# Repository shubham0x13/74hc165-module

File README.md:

# 74HC165 Daisy-Chainable Shift Register Module - Rev 2.0

A simple, compact,  daisy-chainable breakout module based on the **74HC165 8-bit parallel-in/serial-out shift register**. It allows you to add digital inputs to any microcontroller in multiples of 8, using only 3 GPIO pins plus power and ground.

> [!NOTE]
> **Revision History:** Rev 2.0 is the first published release. The unpublished Rev 1.0 had a mirrored input header—while it worked standalone, daisy-chaining with a standard straight-through JST cable would short `VCC` to `GND`. Both headers now share the exact same pin order for safe, plug-and-play chaining. Rev 2.0 also changes the `DIN` termination from a pull-down to a pull-up to align with the default unpressed state of the input pins.

<!-- markdownlint-disable MD033 -->
<div align="center">
  
  &emsp;&emsp;&emsp;&emsp;&emsp;
  
</div>
<!-- markdownlint-enable MD033 -->

## Features & Specs

* **Inputs:** 8 digital inputs via two 5-pin JST-XH headers (4 inputs + shared GND per header).
* **Daisy-Chain:** Connect modules in series to expand inputs in multiples of 8, sharing the same `CLK`, `LOAD`, `VCC`, and `GND` lines.
* **Passives:** Onboard 10 kΩ pull-ups on all inputs, a 100 kΩ pull-up on `DIN` (to ensure that if the MCU reads more bits than are physically connected, the floating/ghost values default to 1, matching the unpressed state of the buttons), and a 100 nF decoupling capacitor.
* **Power:** 2.0V – 6.0V. **Use a VCC compatible with your microcontroller's logic levels** (e.g., 3.3 V for RP2040/ESP32, 5 V for standard Arduino).
* **Dimensions:** 35 × 35 mm (Four M3 mounting holes at 27 × 27 mm).
* **Compatibility:** Standard 74HC165 logic — compatible with DIY firmware such as **FreeJoy** and standard shift-register libraries for **Arduino** (`shiftIn`), **CircuitPython** (`adafruit_74hc165`), and other platforms.

## Pinout

### Chaining Headers (J1 & J2)

Both 5-pin headers share the same pin layout:

1. **VCC:** Power (Match your MCU logic level)
2. **LOAD:** Parallel Load / Latch
3. **CLK:** Clock
4. **DATA:** Serial Data (`DIN` on J1, `DOUT` on J2)
5. **GND:** Ground

**Wiring Guide:**

* **Single Module:** Connect **J2** to your microcontroller. Leave **J1** empty.
* **Daisy-Chaining:** Connect MCU ➔ **J2** (Module 1). Plug Module 1's **J1** ➔ **J2** (Module 2). Repeat for additional modules.

### Button Headers (J3 & J4)

* **D0–D7:** Digital inputs for your buttons/switches.
* **GND:** Shared ground pins.

> [!NOTE]
> Inputs have hardware pull-ups (active-low). Wire your switches directly between `Dx` and `GND`. The MCU will read `1` (HIGH) when open, and `0` (LOW) when pressed.

## Manufacturing & Downloads

<!-- markdownlint-disable MD033 -->
<p align="center">
  
  &emsp;&emsp;
  
</p>
<!-- markdownlint-enable MD033 -->

Ready-to-order fabrication files are available in the [Releases](https://github.com/shubham0x13/74hc165-module/releases) tab. Each release includes:

* **Gerber `.zip` files** (Single board & 4-board panel)
* **Assembly BOMs** (Interactive HTML BOM for easy hand-soldering, plus standard CSV)
* **Schematic PDF** & **STEP 3D Model**

> [!IMPORTANT]
> The 4-board panel (75 × 91 mm) is generated via KiKit and outputs V-score/cut lines on the `User.Comments` layer by default. When ordering the panel, ensure this layer is included in your Gerbers and explicitly request **V-scoring** in your order notes.

## Build Automation

To easily regenerate artifacts after modifying the PCB, a [justfile](justfile) is provided. It uses the KiCad CLI, KiKit, and InteractiveHtmlBom to generate the panel layout, Gerbers, STEP model, BOMs, schematic PDF, and 3D renders.

**Requirements:**

* [KiCad 10.0+](https://www.kicad.org/) (`kicad-cli` must be available in `PATH`)
* [just](https://just.systems/) command runner
* Python 3.10+ (Linux/macOS; Windows uses KiCad's bundled Python)
* [KiKit](https://github.com/yaqwsx/KiKit) (v1.8.1+)
* [InteractiveHtmlBom](https://github.com/openscopeproject/InteractiveHtmlBom) (v2.12.0+)
* **Windows:** Git for Windows (must be in your system PATH to provide `sh.exe` for commands like `rm` and `mkdir`).

**Usage:**

The build system is self-documenting. Run `just` from the repository root to see a list of all available commands and what they do.

```bash
# See all available build commands
just
```

## License

This project is open-source hardware licensed under the **CERN-OHL-S v2**. See [LICENSE](LICENSE) for details.

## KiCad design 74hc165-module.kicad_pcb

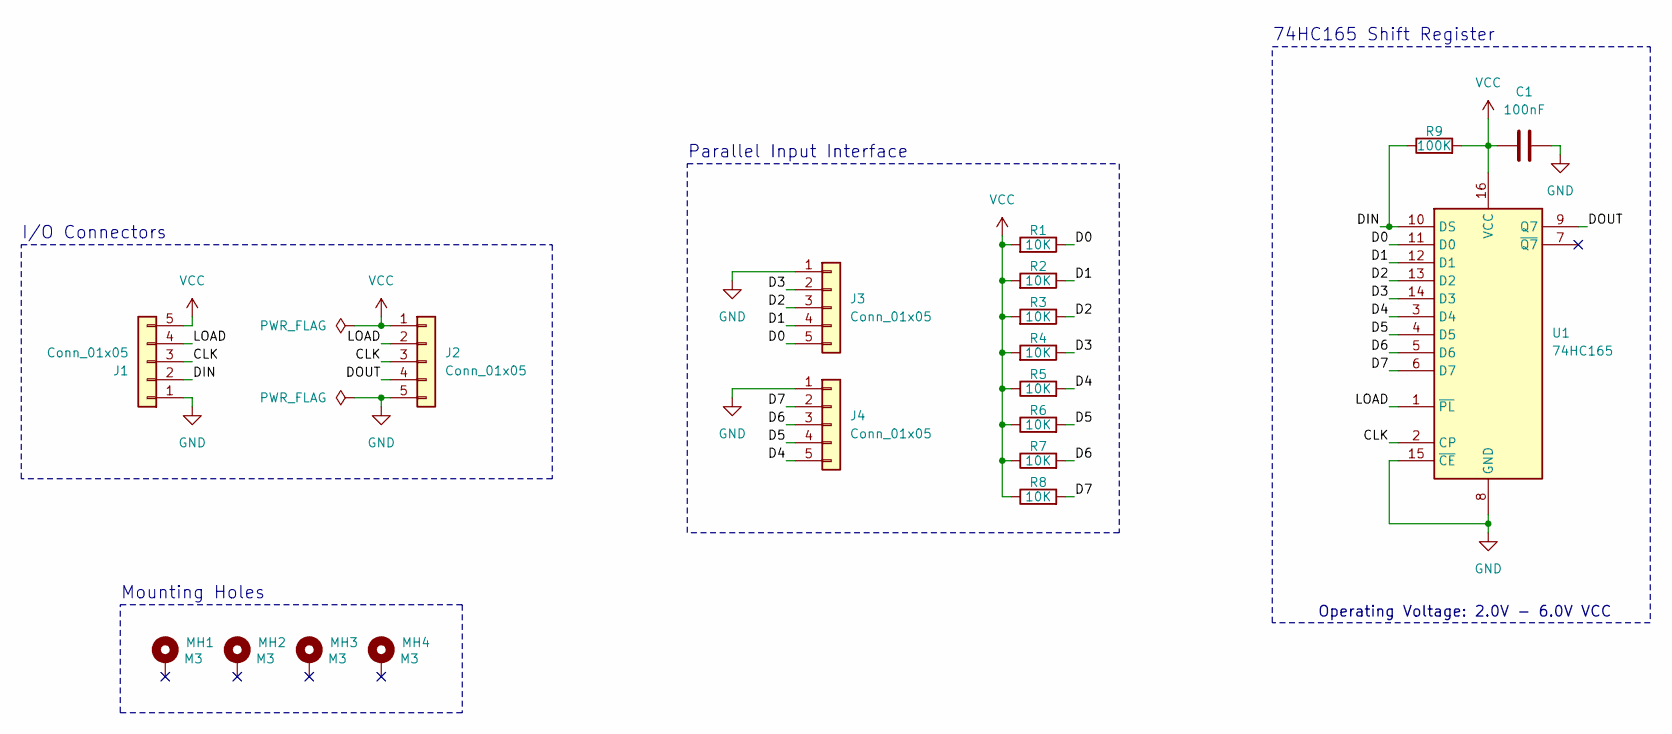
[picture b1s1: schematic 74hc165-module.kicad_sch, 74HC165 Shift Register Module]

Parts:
C1: 100nF; C_0603_1608Metric_Pad1.08x0.95mm_HandSolder
J1, J2, J3, J4: Conn_01x05; JST_XH_B5B-XH-A_1x05_P2.50mm_Vertical
MH1, MH2, MH3, MH4: M3; MountingHole_3.2mm_M3_Pad
R1, R2, R3, R4, R5, R6, R7, R8: 10K; R_0603_1608Metric_Pad0.98x0.95mm_HandSolder
R9: 100K; R_0603_1608Metric_Pad0.98x0.95mm_HandSolder
U1: 74HC165; SOIC-16_3.9x9.9mm_P1.27mm

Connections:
/CLK: J1.3, J2.3, U1.2 (CP)
/D0: J3.5, R1.1, U1.11 (D0)
/D1: J3.4, R2.1, U1.12 (D1)
/D2: J3.3, R3.1, U1.13 (D2)
/D3: J3.2, R4.1, U1.14 (D3)
/D4: J4.5, R5.2, U1.3 (D4)
/D5: J4.4, R6.2, U1.4 (D5)
/D6: J4.3, R7.2, U1.5 (D6)
/D7: J4.2, R8.2, U1.6 (D7)
/DIN: J1.2, R9.1, U1.10 (DS)
/DOUT: J2.4, U1.9 (Q7)
/LOAD: J1.4, J2.2, U1.1 (~PL)
GND: C1.2, J1.1, J2.5, J3.1, J4.1, U1.8 (GND), U1.15 (~CE)
VCC: C1.1, J1.5, J2.1, R1.2, R2.2, R3.2, R4.2, R5.1, R6.1, R7.1, R8.1, R9.2, U1.16 (VCC)

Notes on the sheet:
Parallel Input Interface
I/O Connectors
Operating Voltage: 2.0V - 6.0V VCC
74HC165 Shift Register
Mounting Holes

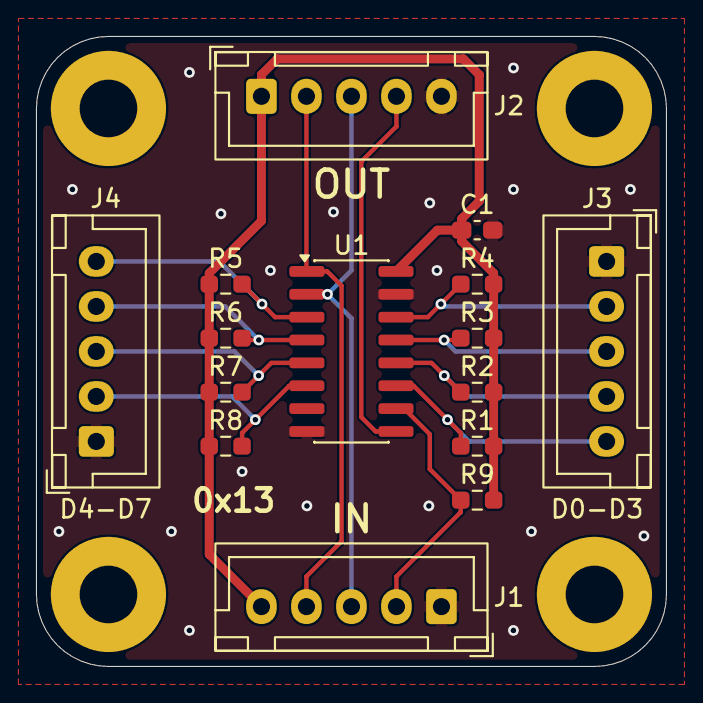
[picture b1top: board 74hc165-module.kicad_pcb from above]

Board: 2 copper layers, 35.0 x 35.0 mm, 19 parts (0 on the bottom side), 14 nets.

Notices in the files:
74hc165-module.kicad_sch:
License: CERN-OHL-S v2
